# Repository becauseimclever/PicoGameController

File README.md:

# PicoGameController
RP2040 based hackable game controller

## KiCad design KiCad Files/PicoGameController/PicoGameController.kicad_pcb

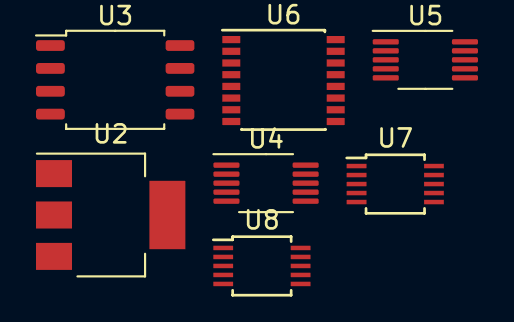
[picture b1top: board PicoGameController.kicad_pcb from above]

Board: 2 copper layers, 7 parts (0 on the bottom side), 3 nets, no tracks yet.

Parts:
U2: NCP1117-3.3_SOT223; SOT-223-3_TabPin2
U3: W25Q128JVS; SOIC-8_5.23x5.23mm_P1.27mm
U4, U5: DRV2605LDGS; VSSOP-10_3x3mm_P0.5mm
U6: UDA1334ATS; SSOP-16_4.4x5.2mm_P0.65mm
U7, U8: ADS1115IDGS; TSSOP-10_3x3mm_P0.5mm

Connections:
+3V3: U2.2 (VO), U3.8 (VCC)
+5V: U4.5 (EN), U4.10 (VDD), U5.5 (EN), U5.10 (VDD), U7.8 (VDD), U8.8 (VDD)
GND: U2.1 (GND), U3.4 (GND), U4.8 (GND), U5.8 (GND), U6.5 (VSSD), U6.15 (VSSA), U7.3 (GND), U8.3 (GND)

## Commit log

2022-01-31 Initial Commit - including rp2040 minimal design
2022-02-02 Adding submodule to make cloning easier
2022-02-02 Adding lots of buttons
2022-02-02 adding more ADCs
2022-02-03 Adding part footprints
2022-02-04 Redoing the buttons
2022-02-09 Adding hierarchel sheets
